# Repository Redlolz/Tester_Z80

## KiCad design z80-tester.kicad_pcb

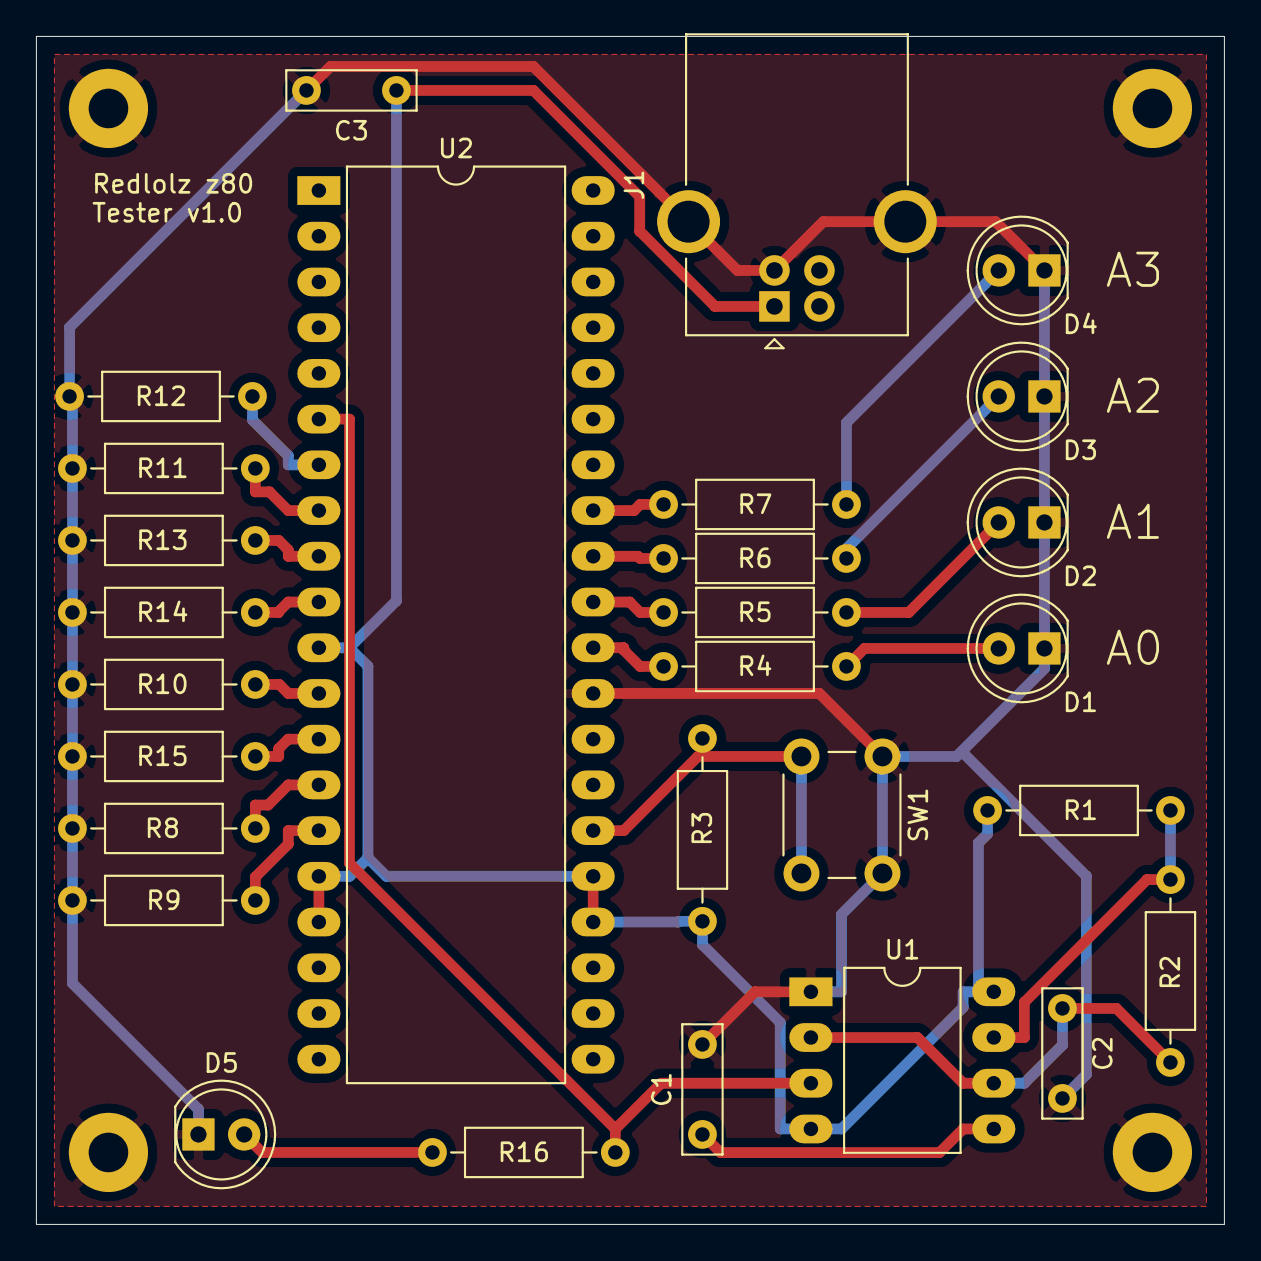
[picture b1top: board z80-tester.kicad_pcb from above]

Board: 2 copper layers, 66.0 x 66.0 mm, 32 parts (0 on the bottom side), 24 nets.

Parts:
C1: 10nF; C_Rect_L7.0mm_W2.0mm_P5.00mm
C2: 1uF; C_Rect_L7.0mm_W2.0mm_P5.00mm
C3: 100nF; C_Rect_L7.0mm_W2.0mm_P5.00mm
D1, D2, D3, D4, D5: LED; LED_D5.0mm
H1, H2, H3, H4: MountingHole_Pad; MountingHole_2.2mm_M2_Pad
J1: USB_B; USB_B_OST_USB-B1HSxx_Horizontal
R1: 1k; R_Axial_DIN0207_L6.3mm_D2.5mm_P10.16mm_Horizontal
R2: 100k; R_Axial_DIN0207_L6.3mm_D2.5mm_P10.16mm_Horizontal
R3, R8, R9, R10, R11, R12, R13, R14, R15: 470; R_Axial_DIN0207_L6.3mm_D2.5mm_P10.16mm_Horizontal
R4, R5, R6, R7, R16: 150; R_Axial_DIN0207_L6.3mm_D2.5mm_P10.16mm_Horizontal
SW1: SW_Push; SW_PUSH_6mm
U1: NE555; DIP-8_W10.16mm_LongPads
U2: Z80CPU; DIP-40_W15.24mm_LongPads

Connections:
+5V: C3.1, J1.1, R1.2, R3.2, U1.4, U1.8, U2.11, U2.16, U2.17, U2.24, U2.25
A0: R4.2, U2.30
A1: R5.2, U2.31
A2: R6.2, U2.32
A3: R7.2, U2.33
D0: R8.2, U2.14
D1: R9.2, U2.15
D2: R10.2, U2.12
D3: R11.2, U2.8
D4: R12.2, U2.7
D5: R13.2, U2.9
D6: R14.2, U2.10
D7: R15.2, U2.13
GND: C1.2, C2.2, C3.2, D1.1, D2.1, D3.1, D4.1, D5.1, H1.1, H2.1, H3.1, H4.1, J1.4, J1.5, R8.1, R9.1, R10.1, R11.1, R12.1, R13.1, R14.1, R15.1, SW1.1, U1.1, U2.29
unnamed: C1.1, U1.5
unnamed: C2.1, R2.1, U1.2, U1.6
unnamed: D1.2, R4.1
unnamed: D2.2, R5.1
unnamed: D3.2, R6.1
unnamed: D4.2, R7.1
unnamed: D5.2, R16.1
unnamed: R1.1, R2.2, U1.7
unnamed: R3.1, SW1.2, U2.26
unnamed: R16.2, U1.3, U2.6

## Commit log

2019-11-15 Added LICENSE & README.md
